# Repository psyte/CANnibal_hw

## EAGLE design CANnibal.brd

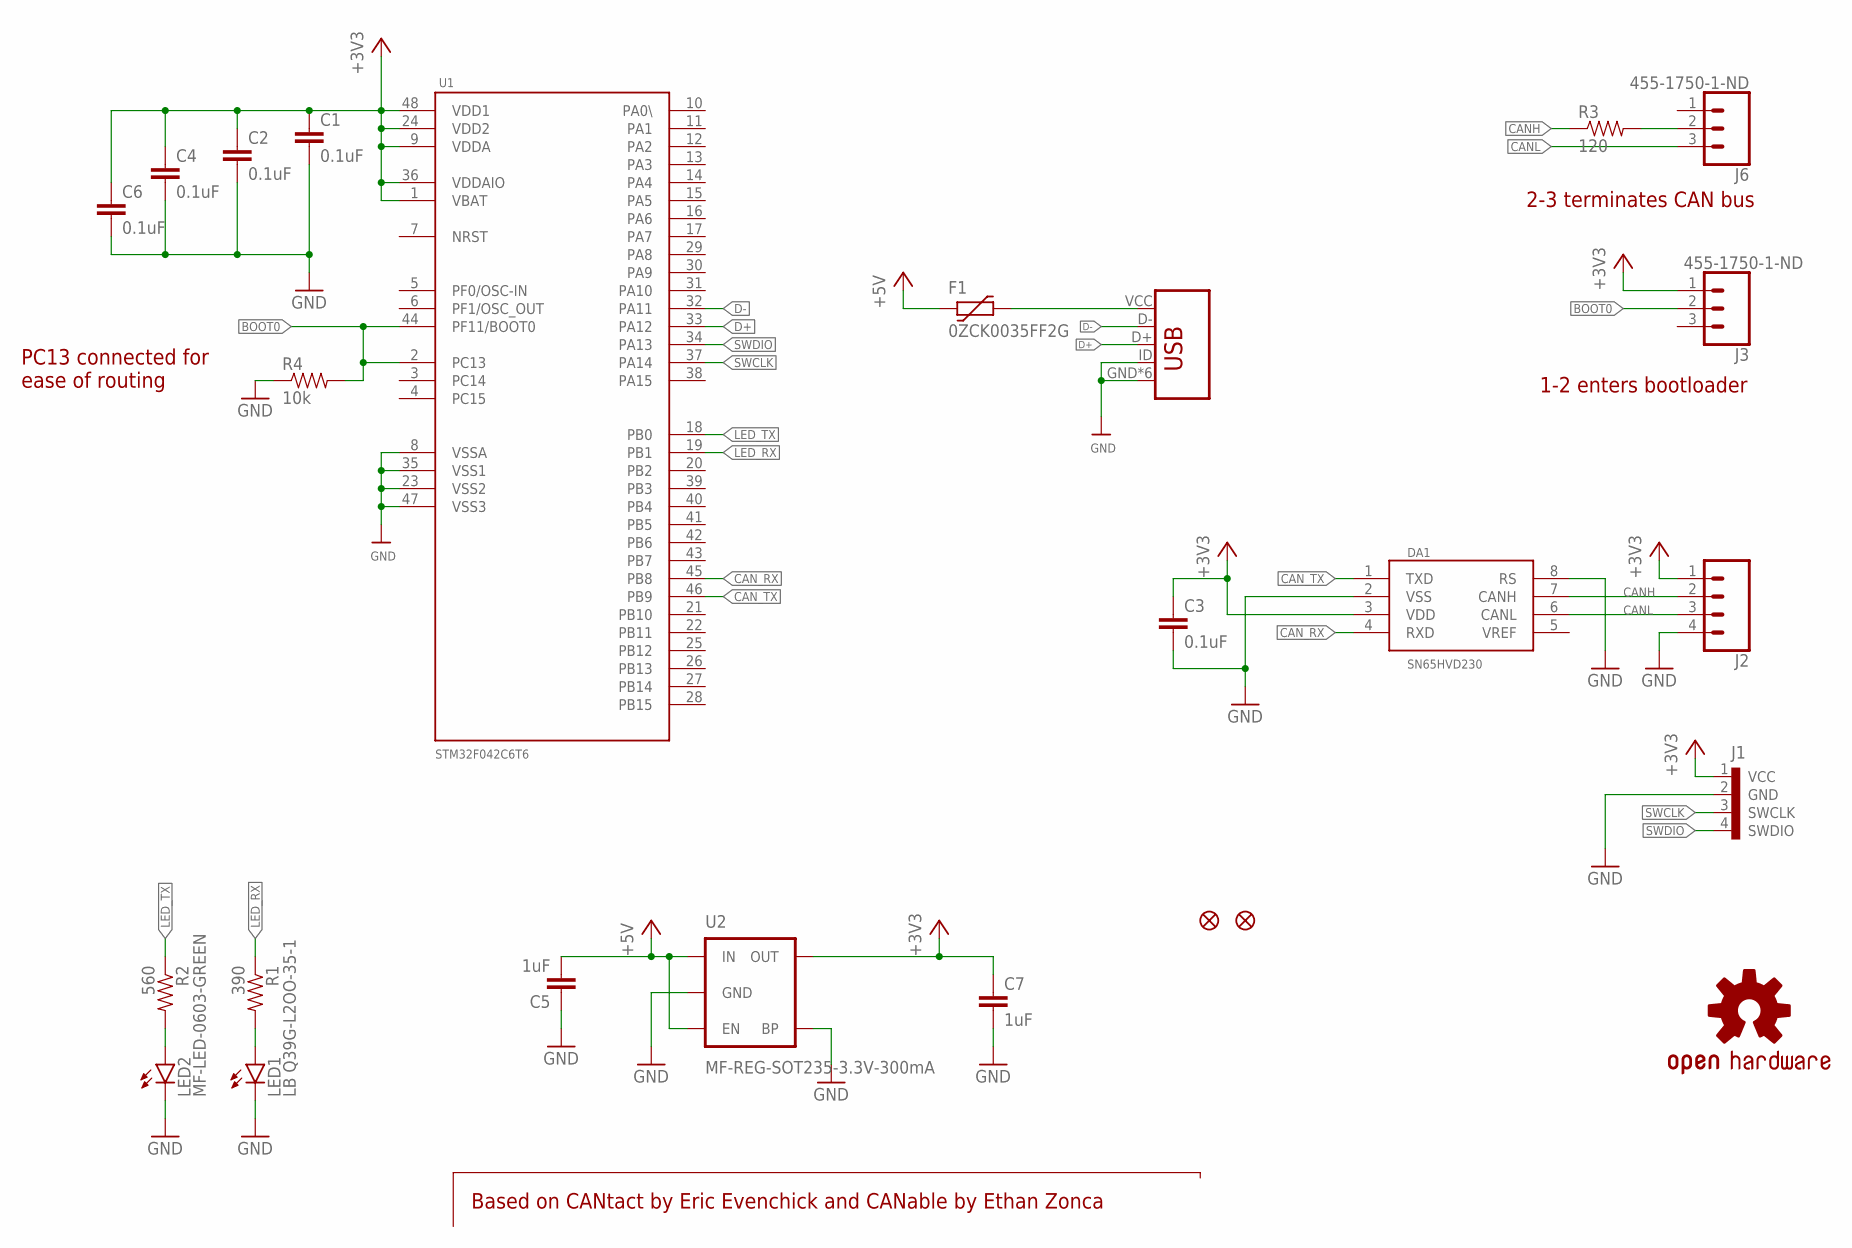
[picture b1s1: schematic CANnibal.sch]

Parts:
C1, C2, C3, C4, C6: 0.1uF; 0603-CAP
C5, C7: 1uF; 0603-CAP
DA1: SN65HVD230; SO08
F1: 0ZCK0035FF2G; PTC0805
FD1, FD2: FIDUCIAL1X2; FIDUCIAL-1X2
J1: POGOPIN-CONN-4; POGOPROG-CONN-4-ALLSMT
J2: CONN_04; 1X04
J3, J6: 455-1750-1-ND; 1X03
LED1: LB Q39G-L2OO-35-1; LED-0603
LED2: MF-LED-0603-GREEN; LED-0603
LOGO1: OSHW-LOGOS; OSHW-LOGO-S
R1: 390; 0603-RES
R2: 560; 0603-RES
R3: 120; 0603-RES
R4: 10k; 0603-RES
U1: STM32F042C6T6; LQFP48
U2: MF-REG-SOT235-3.3V-300mA; SOT23-5
U$4: MICRO-USB-B; MICRO_USB_4_LEGS

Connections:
+3V3: C1.1, C2.1, C3.1, C4.1, C6.1, C7.1, DA1.3 (VDD), J1.1 (VCC), J2.1, J3.1, U1.1 (VBAT), U1.9 (VDDA), U1.24 (VDD2), U1.36 (VDDAIO), U1.48 (VDD1), U2.5 (OUT)
+5V: C5.2, F1.1, U2.1 (IN), U2.3 (EN)
BOOT0: J3.2, R4.2, U1.2 (PC13), U1.44 (PF11/BOOT0)
CANH: DA1.7 (CANH), J2.2, R3.1
CANL: DA1.6 (CANL), J2.3, J6.3
CAN_RX: DA1.4 (RXD), U1.45 (PB8)
CAN_TX: DA1.1 (TXD), U1.46 (PB9)
D+: U1.33 (PA12), U$4.D+
D-: U1.32 (PA11), U$4.D-
GND: C1.2, C2.2, C3.2, C4.2, C5.1, C6.2, C7.2, DA1.2 (VSS), DA1.8 (RS), J1.2 (GND), J2.4, LED1.C, LED2.C, R4.1, U1.8 (VSSA), U1.23 (VSS2), U1.35 (VSS1), U1.47 (VSS3), U2.2 (GND), U2.4 (BP), U$4.GND, U$4.ID, U$4.P$1 (GND), U$4.P$2 (GND), U$4.P$3 (GND), U$4.P$4 (GND), U$4.P$5 (GND)
LED_RX: R1.1, U1.19 (PB1)
LED_TX: R2.1, U1.18 (PB0)
unnamed: LED2.A, R2.2
unnamed: J6.2, R3.2
unnamed: LED1.A, R1.2
SWCLK: J1.3 (SWCLK), U1.37 (PA14)
SWDIO: J1.4 (SWDIO), U1.34 (PA13)
VBUS_RAW: F1.2, U$4.VCC (VBUS)

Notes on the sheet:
Based on CANtact by Eric Evenchick and CANable by Ethan Zonca
PC13 connected for ease of routing
2-3 terminates CAN bus
1-2 enters bootloader

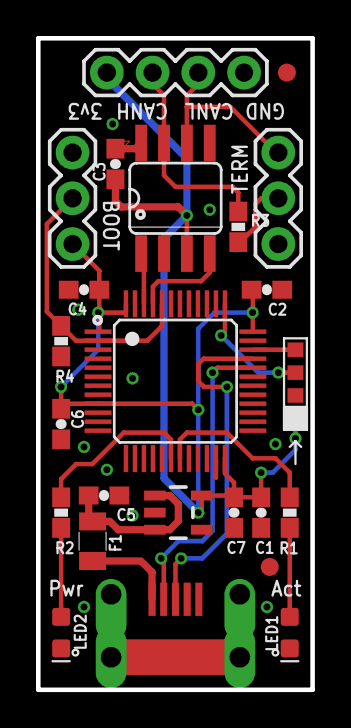
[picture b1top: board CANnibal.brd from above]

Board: 2 copper layers, 15.2 x 36.2 mm, 25 parts (1 on the bottom side), 18 nets.

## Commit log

2018-12-04 Cleanup
2018-12-21 Addes files
2018-12-28 Final version
    Updates USB footprint, fiducials, images, etc
2018-12-28 gitignore: remove *.xln

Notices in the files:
parts and their libraries:
SparkFun-LED: Licensing: Creative Commons ShareAlike 4.0 International - https://creativecommons.org/licenses/by-sa/4.0
